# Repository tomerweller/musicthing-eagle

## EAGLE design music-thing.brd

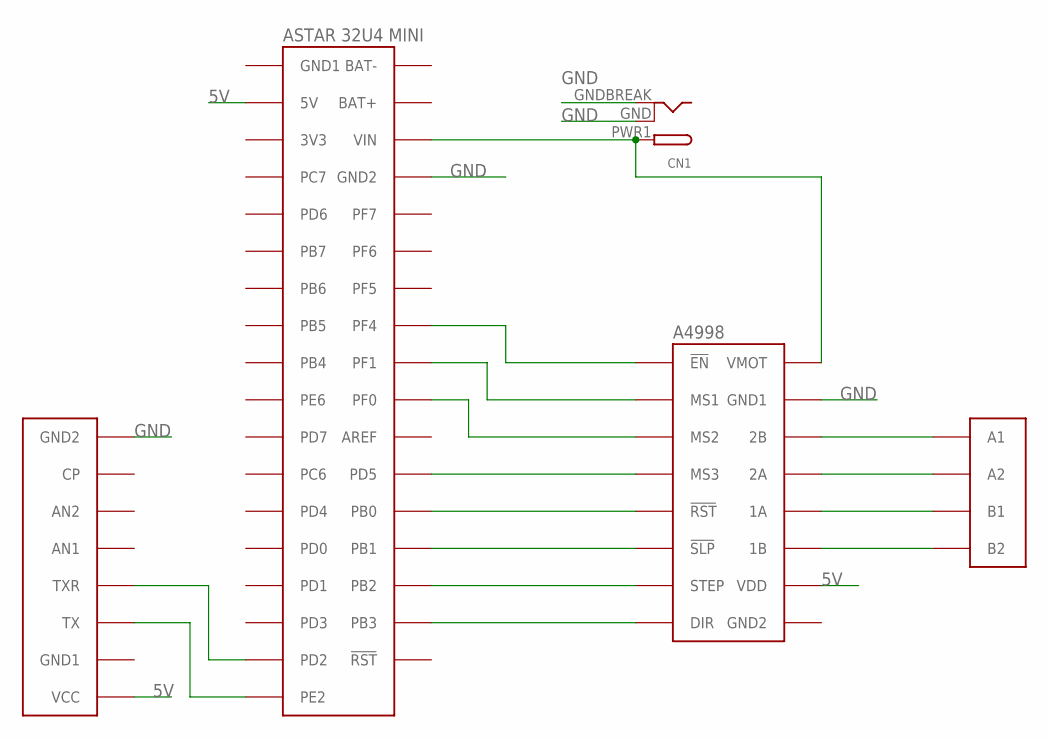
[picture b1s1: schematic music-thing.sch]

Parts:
CN1: DCBARRELSMT; DCJACK_2MM_SMT
U$1: A4998
U$2: ASTAR32U4MINI
U$3: CON-USB-READER-V18
U$4: CON-MOTOR

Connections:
5V: U$1.VDD, U$2.5V, U$3.VCC
GND: CN1.GND (GNDBREAK), CN1.GNDBREAK (GND), U$1.GND1, U$2.GND2, U$3.GND2
unnamed: U$1.2B, U$4.A1
unnamed: U$1.2A, U$4.A2
unnamed: U$1.1A, U$4.B1
unnamed: U$1.1B, U$4.B2
unnamed: U$1.DIR, U$2.PB3
unnamed: U$1.STP (STEP), U$2.PB2
unnamed: U$1.!SLP, U$2.PB1
unnamed: U$1.!RST, U$2.PB0
unnamed: U$1.MS3, U$2.PD5
unnamed: U$1.MS2, U$2.PF0
unnamed: U$1.MS1, U$2.PF1
unnamed: U$1.!EN, U$2.PF4
unnamed: U$2.PE2, U$3.TX
unnamed: U$2.PD2, U$3.TXR
unnamed: CN1.PWR1 (PWR), U$1.VMOT, U$2.VIN

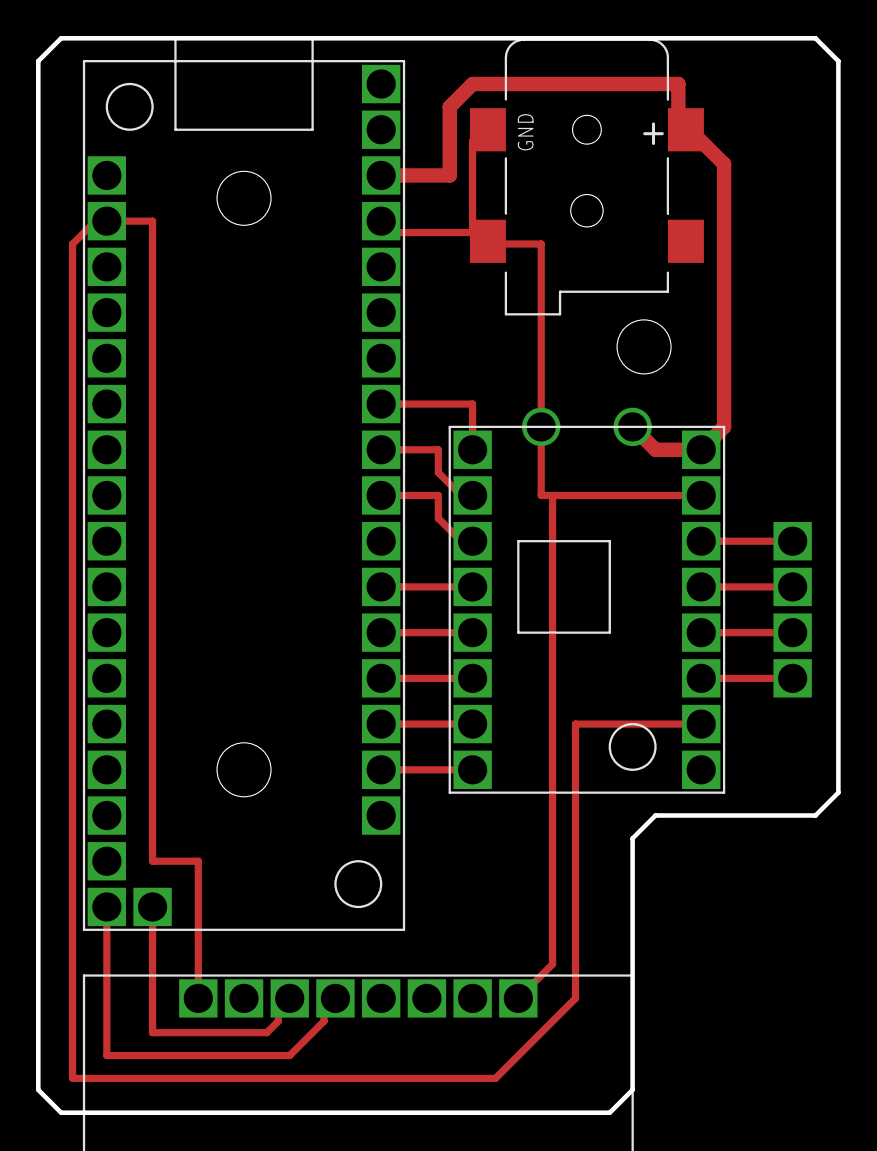
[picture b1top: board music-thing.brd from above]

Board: 2 copper layers, 44.5 x 59.7 mm, 5 parts (0 on the bottom side), 17 nets.

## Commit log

2016-11-08 init
2016-11-08 finalize
2016-11-08 new board
2016-11-08 new layout
